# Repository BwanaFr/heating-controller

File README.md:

# Heating controller

## Presentation
This project is a IOT hardware heater controller for floor heat cumulating heaters (not sure about english term).
These heaters where mainly installed in France.
The principle is to store heat in the concrete floor during nights (when nuclear plants are free) to be restored during the day.

The heater can be controlled using MQTT using a Wi-Fi connection or using the integrated OLED display.
It is designed to be mounted on a DIN rail in an electrical cabinet.

## Hardware
Hardware design files are located in the hardware folder.
Schematics and PCB is designed using Kicad.

# Software
Microcontroller firmware is located in the software folder.
This is a PlatformIO project.

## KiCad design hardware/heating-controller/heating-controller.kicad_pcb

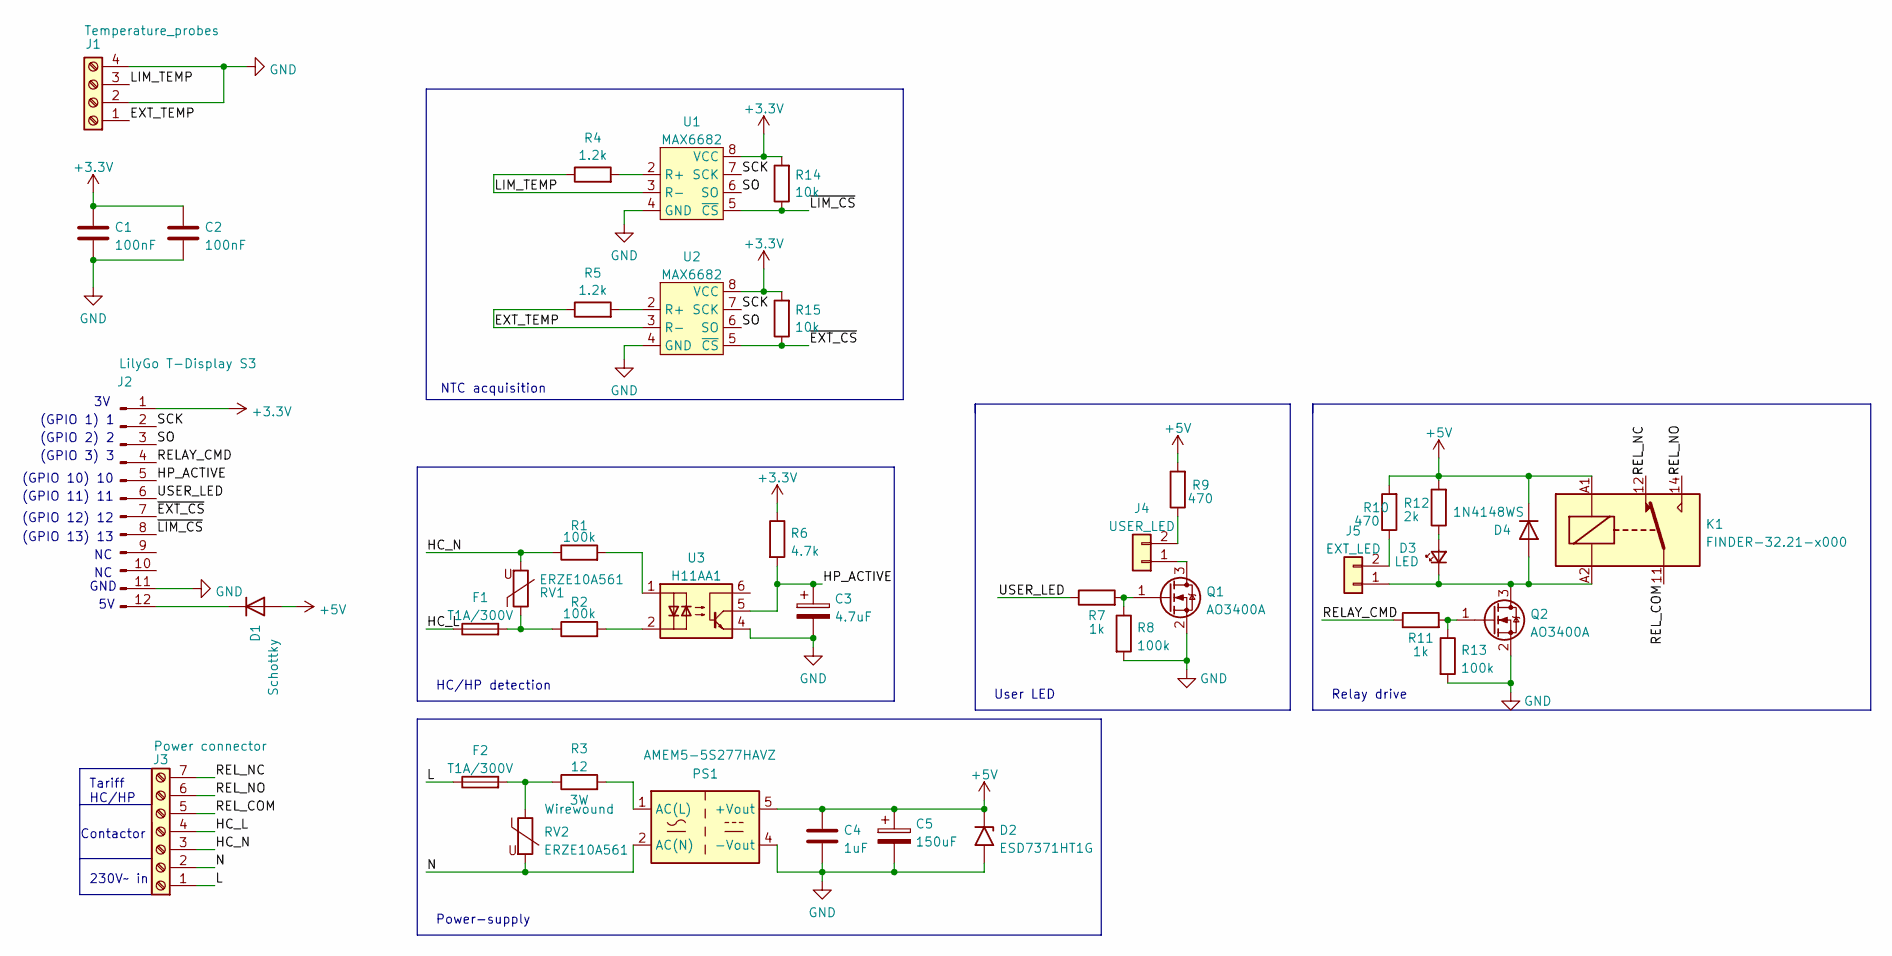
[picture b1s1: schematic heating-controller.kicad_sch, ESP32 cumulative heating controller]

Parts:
C1, C2: 100nF; C_0603_1608Metric_Pad1.08x0.95mm_HandSolder
C3: 4.7uF; C_1206_3216Metric
C4: 1uF; C_0603_1608Metric
C5: 150uF; C_Radial_D10.0mm_H12.5mm_P5.00mm
D1: Schottky; D_SOD-123
D2: ESD7371HT1G; D_SOD-323_HandSoldering
D3: LED; LED_0805_2012Metric
D4: 1N4148WS; D_SOD-323
F1, F2: T1A/300V; Fuse_Littelfuse_372_D8.50mm
J1: Temperature_probes; TerminalBlock_Phoenix_MKDS-3-4-5.08_1x04_P5.08mm_Horizontal
J2: LilyGo T-Display S3; PinHeader_1x12_P2.54mm_Vertical
J3: Power connector; TerminalBlock_Phoenix_MKDS-3-7-5.08_1x07_P5.08mm_Horizontal
J4: USER_LED; PinHeader_1x02_P2.54mm_Vertical
J5: EXT_LED; PinHeader_1x02_P2.54mm_Vertical
K1: FINDER-32.21-x000; Relay_SPDT_Finder_32.21-x000
PS1: AMEM5-5S277HAVZ; Converter_ACDC_Murata_BAC05SxxDC_THT
Q1, Q2: AO3400A; SOT-23
R1, R2: 100k; R_Axial_DIN0204_L3.6mm_D1.6mm_P5.08mm_Horizontal
R3: 12; R_Axial_DIN0614_L14.3mm_D5.7mm_P15.24mm_Horizontal
R4, R5: 1.2k; R_0603_1608Metric
R6: 4.7k; R_0603_1608Metric
R7, R11: 1k; R_0603_1608Metric
R8, R13: 100k; R_0603_1608Metric
R9, R10: 470; R_0603_1608Metric
R12: 2k; R_0603_1608Metric
R14, R15: 10k; R_0603_1608Metric
RV1, RV2: ERZE10A561; RV_Disc_D12mm_W7.5mm_P7.5mm
U1, U2: MAX6682; MSOP-8_3x3mm_P0.65mm
U3: H11AA1; DIP-6_W7.62mm

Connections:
+3.3V: C1.1, C2.1, J2.1, R6.1, R14.2, R15.2, U1.8 (VCC), U2.8 (VCC)
+5V: C4.1, C5.1, D1.2 (A), D2.1 (A1), D4.1 (K), K1.A1, PS1.5 (+Vout), R9.2, R10.2, R12.2
/EXT_TEMP: J1.1, R5.1, U2.3 (R-)
/HC_L: F1.1, J3.4
/HC_N: J3.3, R1.1, RV1.2
/HP_ACTIVE: C3.1, J2.5, R6.2, U3.5
/L: F2.1, J3.1
/LIM_TEMP: J1.3, R4.1, U1.3 (R-)
/N: J3.2, PS1.2 (AC(N)), RV2.2
/RELAY_CMD: J2.4, R11.1
/REL_COM: J3.5, K1.11
/REL_NC: J3.7, K1.12
/REL_NO: J3.6, K1.14
/SCK: J2.2, U1.7 (SCK), U2.7 (SCK)
/SO: J2.3, U1.6 (SO), U2.6 (SO)
/USER_LED: J2.6, R7.1
/~EXT_CS: J2.7, R15.1, U2.5 (~CS)
/~LIM_CS: J2.8, R14.1, U1.5 (~CS)
GND: C1.2, C2.2, C3.2, C4.2, C5.2, D2.2 (A2), J1.2, J1.4, J2.11, PS1.4 (-Vout), Q1.2 (S), Q2.2 (S), R8.2, R13.2, U1.4 (GND), U2.4 (GND), U3.4
unnamed: D1.1 (K), J2.12
unnamed: D3.2 (A), R12.1
unnamed: D3.1 (K), D4.2 (A), J5.1, K1.A2, Q2.3 (D)
unnamed: F1.2, R2.1, RV1.1
unnamed: F2.2, R3.1, RV2.1
unnamed: J4.1, Q1.3 (D)
unnamed: J4.2, R9.1
unnamed: J5.2, R10.1
unnamed: PS1.1 (AC(L)), R3.2
unnamed: Q1.1 (G), R7.2, R8.1
unnamed: Q2.1 (G), R11.2, R13.1
unnamed: R1.2, U3.1
unnamed: R2.2, U3.2
unnamed: R4.2, U1.2 (R+)
unnamed: R5.2, U2.2 (R+)

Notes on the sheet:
(GPIO 10) 10
(GPIO 12) 12
User LED
(GPIO 13) 13
Contactor
GND
Power-supply
NTC acquisition
Tariff HC/HP
(GPIO 11) 11
(GPIO 2) 2
230V~ in
(GPIO 3) 3
(GPIO 1) 1
Relay drive
HC/HP detection

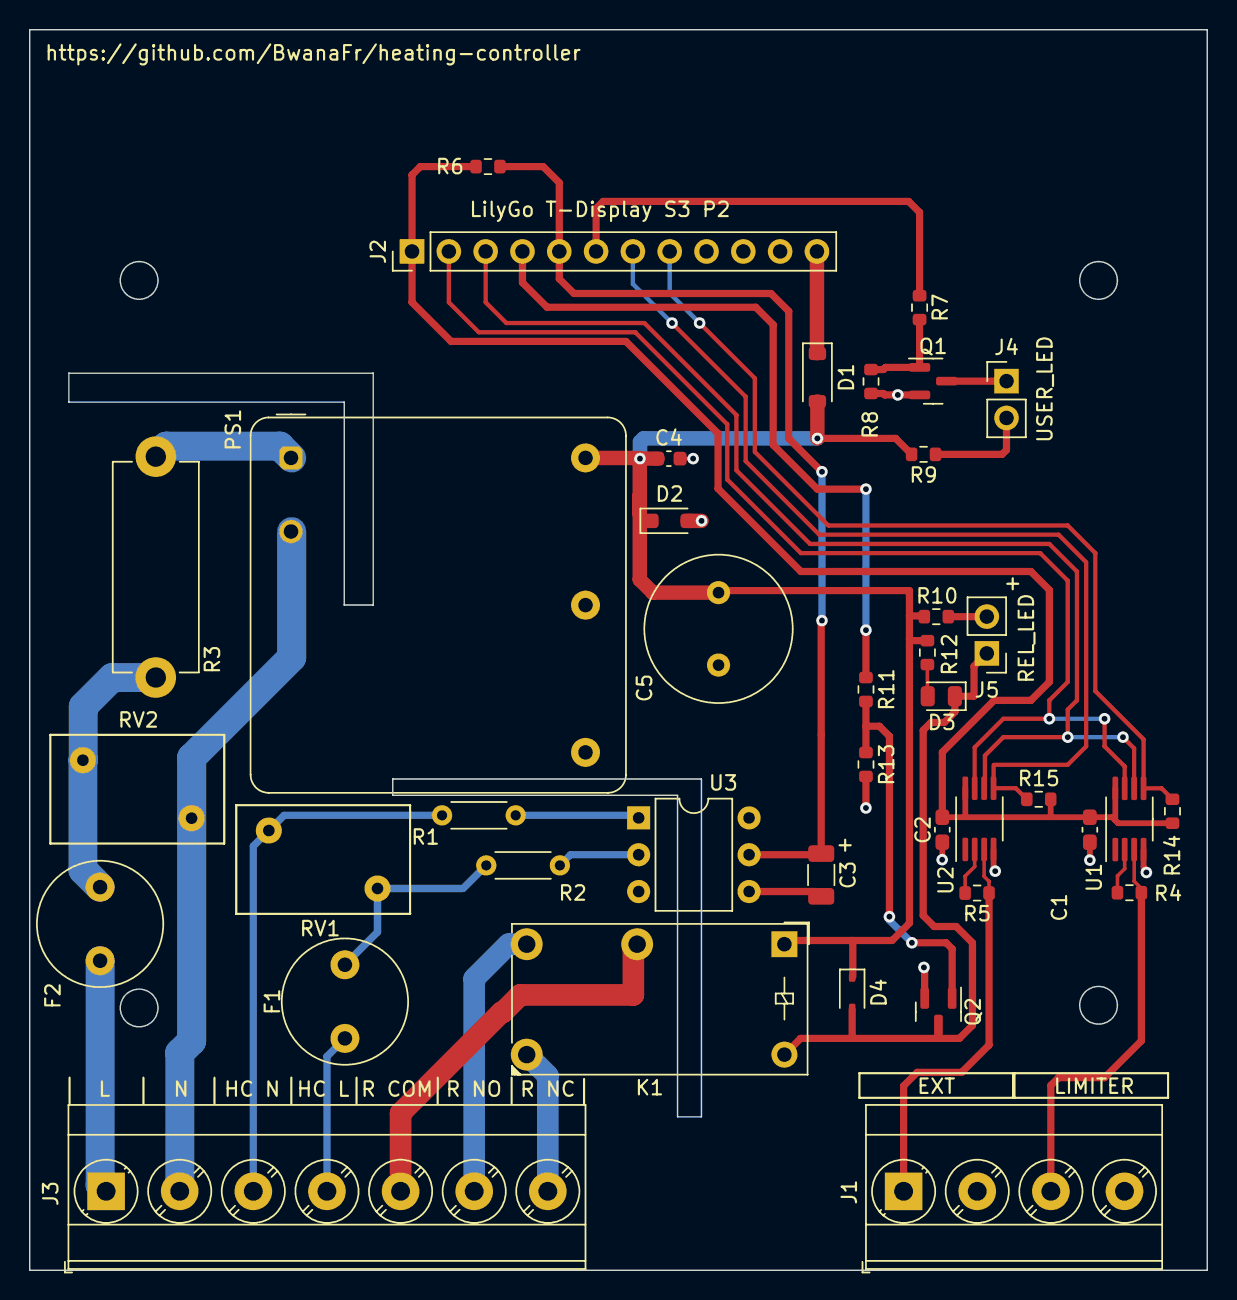
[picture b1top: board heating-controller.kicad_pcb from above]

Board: 2 copper layers, 81.2 x 85.6 mm, 40 parts (0 on the bottom side), 34 nets.

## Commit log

2022-11-23 First PCB, needs to be checked
2022-12-21 Added 10uF capacitors to NTC
2022-12-21 Progress on UI
2023-01-10 Added screen blanking
2023-01-13 Added startup screen
2023-03-23 Added process for controlling relay
2023-03-23 Fixed boolean display labels
2023-03-24 Started MQTT implementation
2023-03-29 Added LVGL simulator support
2023-03-29 Working on UI
2023-03-31 Working on home UI
2023-03-31 WIP on home screen
2023-04-04 Added MQTT UI
2023-04-12 Working on setup UI
2023-04-12 WIP on setup UI
2023-04-14 Needs settings manager
2023-04-17 WIP on UI
2023-04-18 WIP again and again
2023-04-18 Fixed compilation warnings
2023-04-19 WIP, added setup controls
2023-04-19 Added validators for profile settings
2023-04-19 Added simple MQTT
2023-04-21 WIP, approaching first release!
2023-04-25 Added OTA and MQTT reconnection in separate task
2023-04-25 Renamed profiles
2023-04-25 Added MAC address in info
2023-04-28 Begin to support newer T-Display-S3
2023-05-02 Fixed back button handling
2023-05-03 Fixed screen unblanking artefacts
2023-05-23 Added T-Display board
2023-05-26 Removed USB serial device, call LV more often
2023-06-16 Trying to fix screen blanking
2023-06-19 Screen blanking improvements
2023-07-17 Added .gitignore
2023-09-19 Improving ADC precision
2023-09-20 Migrated to KiCad 7 and remove custom AC/DC
2023-10-09 MAX682 hardware
2023-10-10 WIP on firmware
2023-10-31 Replaced SPI by bitbang
